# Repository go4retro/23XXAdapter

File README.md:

# 23XXAdapter
MOS 2316/32/64 to JEDEC 27XX(X) Adapter

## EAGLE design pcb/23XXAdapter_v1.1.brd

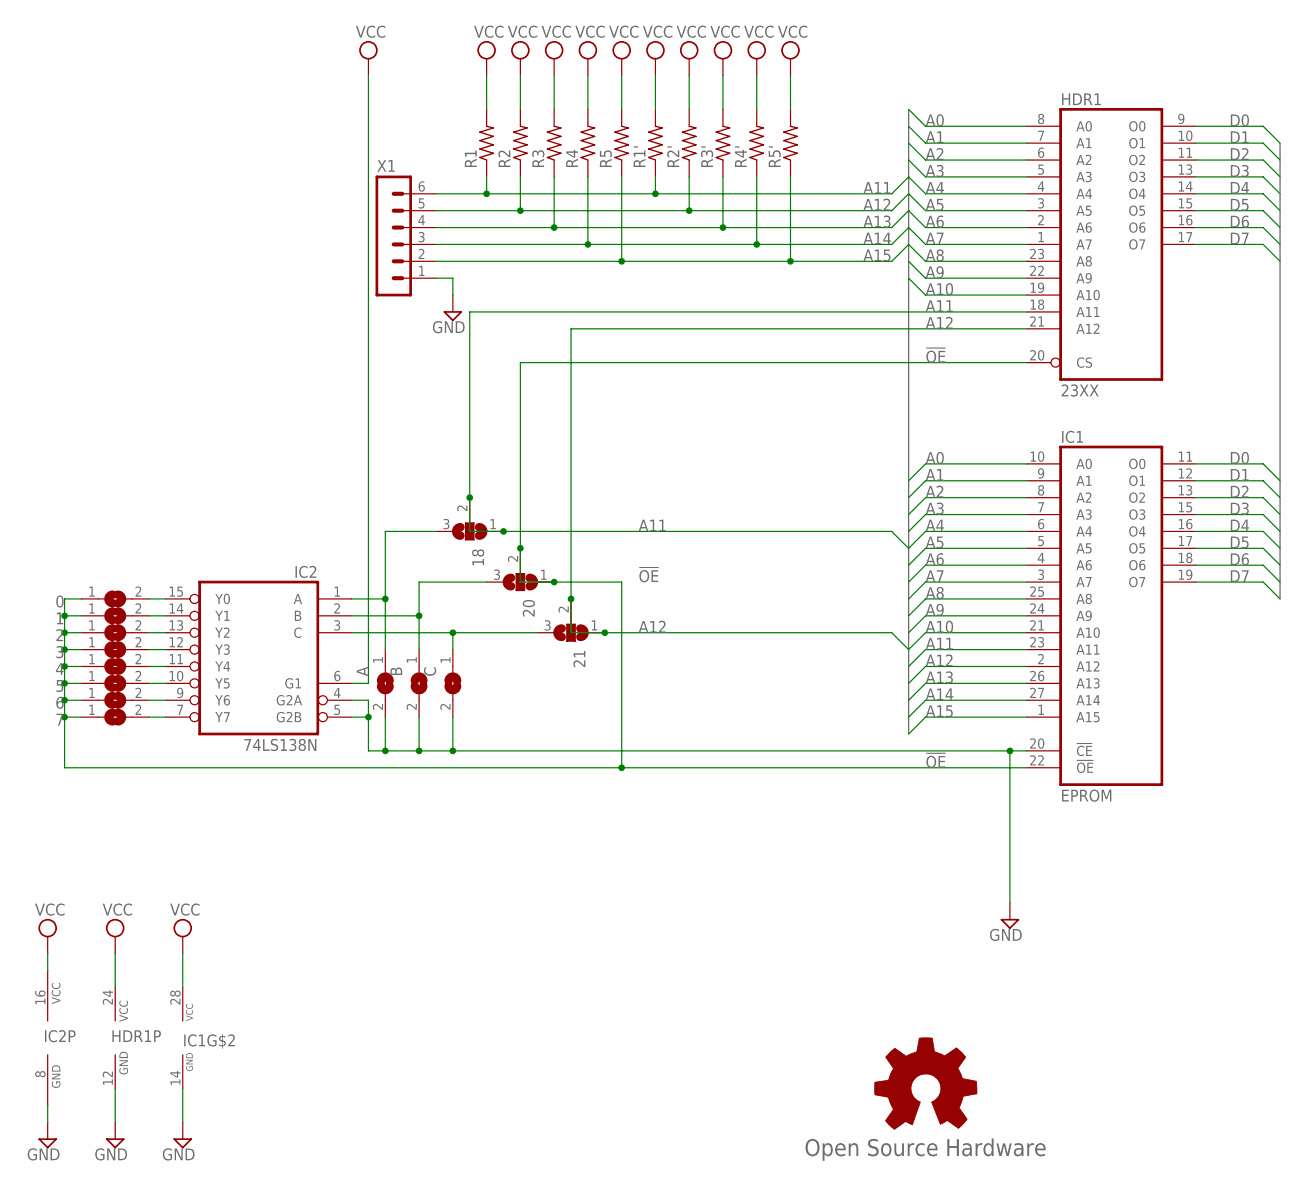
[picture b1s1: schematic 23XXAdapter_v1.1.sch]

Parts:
0, 1, 2, 3, 4, 5, 6, 7: SJ
18, 20, 21: SJ2W; SJ_2
A: SJ
B: SJ
C: SJ
GOLD_ORB_SM1: Open Source Hardware; OSHW_5MM
HDR1: 23XX; DIL24-ROUNDPAD
IC1: EPROM; DIL28-ROUNDPAD
IC2: 74LS138N; DIL16-RP
R1, R2, R3, R4, R5: R-US_0204/5; 0204/5
R1', R2', R3', R4', R5': R-US_R0805; R0805
X1: MA06-1

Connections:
!OE: 0.1, 1.1, 2.1, 3.1, 4.1, 5.1, 6.1, 7.1, 20.1, 20.2, HDR1.20 (CS), IC1.22 (!OE)
A0: HDR1.8 (A0), IC1.10 (A0)
A1: HDR1.7 (A1), IC1.9 (A1)
A2: HDR1.6 (A2), IC1.8 (A2)
A3: HDR1.5 (A3), IC1.7 (A3)
A4: HDR1.4 (A4), IC1.6 (A4)
A5: HDR1.3 (A5), IC1.5 (A5)
A6: HDR1.2 (A6), IC1.4 (A6)
A7: HDR1.1 (A7), IC1.3 (A7)
A8: HDR1.23 (A8), IC1.25 (A8)
A9: HDR1.22 (A9), IC1.24 (A9)
A10: HDR1.19 (A10), IC1.21 (A10)
A11: 18.1, 18.2, HDR1.18 (A11), IC1.23 (A11), R1.1, R1'.1, X1.6
A12: 21.1, 21.2, HDR1.21 (A12), IC1.2 (A12), R2.1, R2'.1, X1.5
A13: IC1.26 (A13), R3.1, R3'.1, X1.4
A14: IC1.27 (A14), R4.1, R4'.1, X1.3
A15: IC1.1 (A15), R5.1, R5'.1, X1.2
D0: HDR1.9 (O0), IC1.11 (O0)
D1: HDR1.10 (O1), IC1.12 (O1)
D2: HDR1.11 (O2), IC1.13 (O2)
D3: HDR1.13 (O3), IC1.15 (O3)
D4: HDR1.14 (O4), IC1.16 (O4)
D5: HDR1.15 (O5), IC1.17 (O5)
D6: HDR1.16 (O6), IC1.18 (O6)
D7: HDR1.17 (O7), IC1.19 (O7)
GND: A.2, B.2, C.2, HDR1.12 (GND), IC1.14 (GND), IC1.20 (!CE), IC2.4 (G2A), IC2.5 (G2B), IC2.8 (GND), X1.1
unnamed: 20.3, B.1, IC2.2 (B)
unnamed: 0.2, IC2.15 (Y0)
unnamed: 1.2, IC2.14 (Y1)
unnamed: 2.2, IC2.13 (Y2)
unnamed: 3.2, IC2.12 (Y3)
unnamed: 4.2, IC2.11 (Y4)
unnamed: 5.2, IC2.10 (Y5)
unnamed: 6.2, IC2.9 (Y6)
unnamed: 7.2, IC2.7 (Y7)
unnamed: 21.3, C.1, IC2.3 (C)
unnamed: 18.3, A.1, IC2.1 (A)
VCC: HDR1.24 (VCC), IC1.28 (VCC), IC2.6 (G1), IC2.16 (VCC), R1.2, R1'.2, R2.2, R2'.2, R3.2, R3'.2, R4.2, R4'.2, R5.2, R5'.2

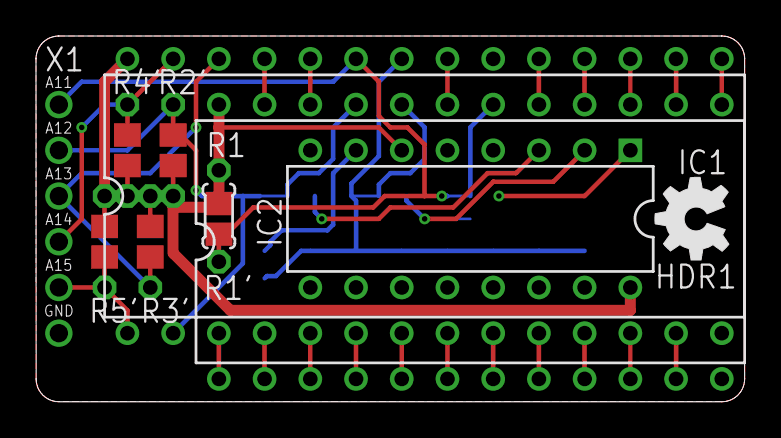
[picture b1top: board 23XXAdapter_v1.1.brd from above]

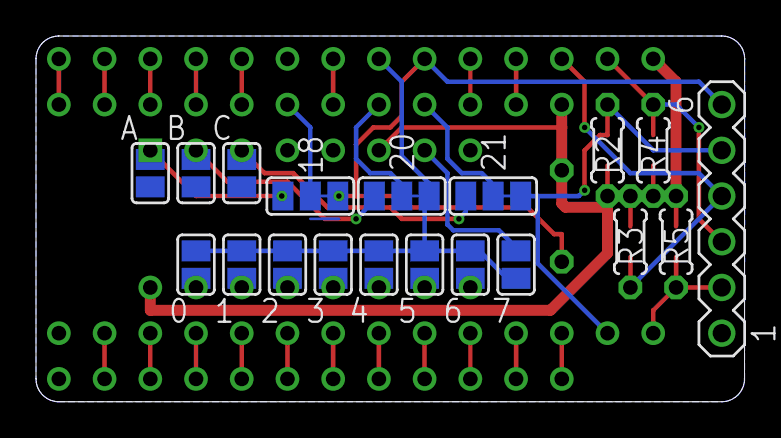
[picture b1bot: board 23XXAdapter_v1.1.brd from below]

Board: 2 copper layers, 39.4 x 20.3 mm, 29 parts (19 on the bottom side), 38 nets.

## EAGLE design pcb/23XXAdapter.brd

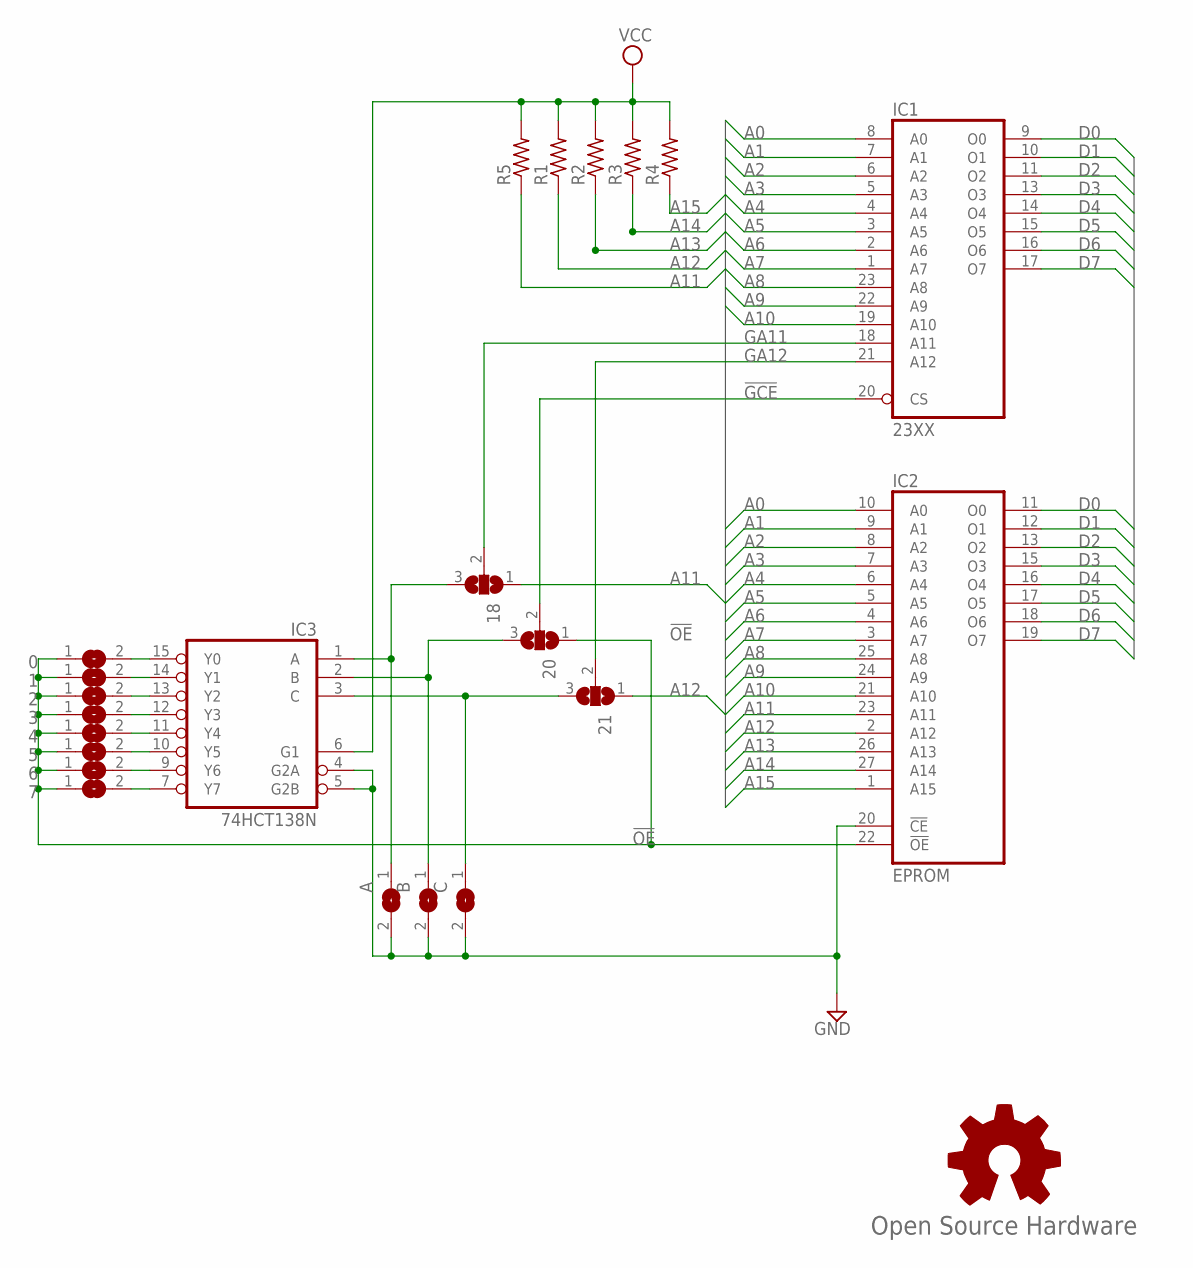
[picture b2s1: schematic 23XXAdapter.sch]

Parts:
0, 1, 2, 3, 4, 5, 6, 7: SJ
18, 20, 21: SJ2W; SJ_2
A: SJ
B: SJ
C: SJ
GOLD_ORB_SM1: Open Source Hardware; OSHW_5MM
IC1: 23XX; DIL24-ROUNDPAD
IC2: EPROM; DIL28-ROUNDPAD
IC3: 74HCT138N; DIL16
R1, R2, R3, R4, R5: R-US_0204/5; 0204/5

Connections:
!GCE: 20.2, IC1.20 (CS)
!OE: 0.1, 1.1, 2.1, 3.1, 4.1, 5.1, 6.1, 7.1, 20.1, IC2.22 (!OE)
A0: IC1.8 (A0), IC2.10 (A0)
A1: IC1.7 (A1), IC2.9 (A1)
A2: IC1.6 (A2), IC2.8 (A2)
A3: IC1.5 (A3), IC2.7 (A3)
A4: IC1.4 (A4), IC2.6 (A4)
A5: IC1.3 (A5), IC2.5 (A5)
A6: IC1.2 (A6), IC2.4 (A6)
A7: IC1.1 (A7), IC2.3 (A7)
A8: IC1.23 (A8), IC2.25 (A8)
A9: IC1.22 (A9), IC2.24 (A9)
A10: IC1.19 (A10), IC2.21 (A10)
A11: 18.1, IC2.23 (A11), R5.1
A12: 21.1, IC2.2 (A12), R1.1
A13: IC2.26 (A13), R2.1
A14: IC2.27 (A14), R3.1
A15: IC2.1 (A15), R4.1
D0: IC1.9 (O0), IC2.11 (O0)
D1: IC1.10 (O1), IC2.12 (O1)
D2: IC1.11 (O2), IC2.13 (O2)
D3: IC1.13 (O3), IC2.15 (O3)
D4: IC1.14 (O4), IC2.16 (O4)
D5: IC1.15 (O5), IC2.17 (O5)
D6: IC1.16 (O6), IC2.18 (O6)
D7: IC1.17 (O7), IC2.19 (O7)
GA11: 18.2, IC1.18 (A11)
GA12: 21.2, IC1.21 (A12)
GND: A.2, B.2, C.2, IC1.12 (GND), IC2.14 (GND), IC2.20 (!CE), IC3.4 (G2A), IC3.5 (G2B), IC3.8 (GND)
unnamed: 20.3, B.1, IC3.2 (B)
unnamed: 0.2, IC3.15 (Y0)
unnamed: 1.2, IC3.14 (Y1)
unnamed: 2.2, IC3.13 (Y2)
unnamed: 3.2, IC3.12 (Y3)
unnamed: 4.2, IC3.11 (Y4)
unnamed: 5.2, IC3.10 (Y5)
unnamed: 6.2, IC3.9 (Y6)
unnamed: 7.2, IC3.7 (Y7)
unnamed: 21.3, C.1, IC3.3 (C)
unnamed: 18.3, A.1, IC3.1 (A)
VCC: IC1.24 (VCC), IC2.28 (VCC), IC3.6 (G1), IC3.16 (VCC), R1.2, R2.2, R3.2, R4.2, R5.2

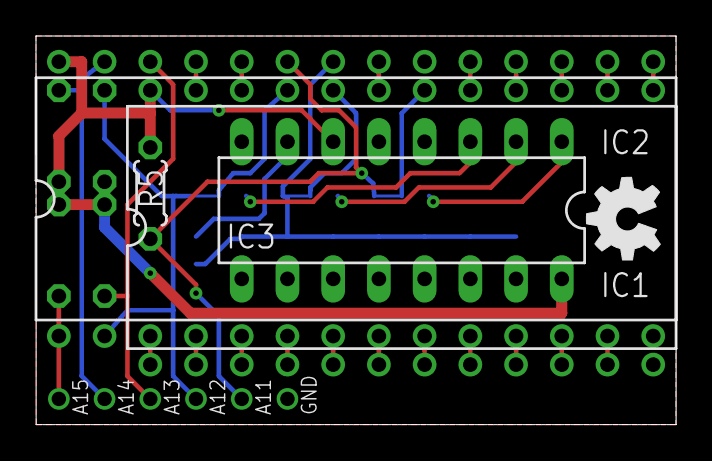
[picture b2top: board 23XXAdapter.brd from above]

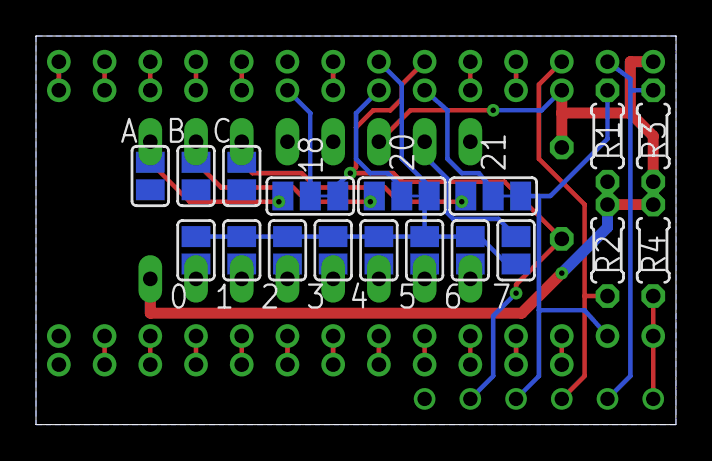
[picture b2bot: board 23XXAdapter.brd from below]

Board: 2 copper layers, 35.6 x 21.6 mm, 23 parts (18 on the bottom side), 41 nets.

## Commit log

2018-03-11 Fix README.txt
2018-03-11 Updated license
2018-03-11 Added README.md
2020-10-11 Added BOM and updates to PCB
2023-02-22 Update schematic to show VCC/GND and pre-connected pads, h/t Mike Forster
2025-08-09 PCB cleanup and additional images

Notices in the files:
pcb/23XXAdapter.brd:
(c) 2012 RETRO Innovations
pcb/23XXAdapter_v1.1.brd:
(c) 2012-24
